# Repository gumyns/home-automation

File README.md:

# Licenses
Code: [Apache 2.0](./LICENSE) ([tl;dr](https://choosealicense.com/licenses/apache-2.0/))

PCB: [CC-BY](./CC-BY.md) ([tl;dr](https://creativecommons.org/licenses/by/4.0/))

# What is it?
STM32 ARM based home automation system. Devices are built with STM32 F0 series microcontrollers (mostly with [STM32F030F4](http://www.st.com/en/microcontrollers/stm32f0x0-value-line.html?querycriteria=productId=LN1826), cheapest one). Project provides also a plugin for [OpenHab2](http://docs.openhab.org/) ([demo](http://demo.openhab.org:8080/start/index)), that allows integration also with other automation systems.

## Architecture
Generally it looks like this:

computer <=> gateway <=> hub <=> device 

On top there's a computer with OpenHab2 running with plugin configured (e.g. PC, RaspberryPi, Odroid, whatever that can run Java8).

Gateway is some cheap ARM based board with Linux, like Rasperry Zero, NanoPi, and communicates with central computer utilizing distributed system built on top of TCP/IP.

Hub is an ARM based board, that can communicate with gateway using any of supported protocols, and can communicate with devices. Amount of ports is configurable.

Device is just a worker (also ARM based board), that communitates with hubs using specific protocol, and provides data to the system.

#### This repository contains following modules
##### - [OpenHab2 plugin](./openhab2)
##### - [C++ server and plugins for gateways](./server)
##### - [PCB layouts and microcontrollers code](./hardware)

# NOTE
This project is in early stage, it's already a working prototype but far from final product.

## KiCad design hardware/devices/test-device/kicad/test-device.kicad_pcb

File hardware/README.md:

## Prerequisites
Download gcc-arm: http://gnuarmeclipse.github.io/toolchain/install/

Generate toolchains and cmake files, call this:
```commandline
python prepare.py
```

Download CubeMX package for STM32F0, or whole STM32CubeMX
```
http://www.st.com/en/embedded-software/stm32cubef0.html
```

## Building
Setup proper toolchain for correct device:
```commandline
mkdir build 
cd build 
cmake .. -DCMAKE_TOOLCHAIN_FILE=../toolchains/STM32F030x6.cmake
```

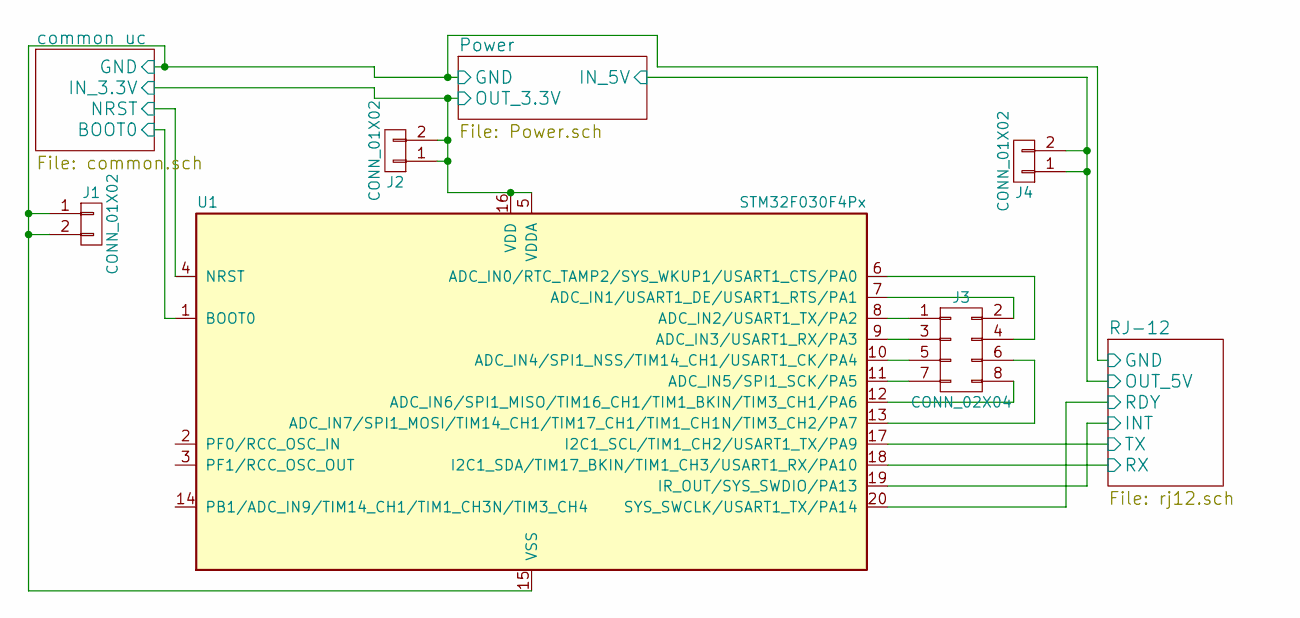
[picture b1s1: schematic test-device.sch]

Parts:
J1, J2, J4: CONN_01X02; Pin_Header_Straight_1x02_Pitch2.54mm
J3: CONN_02X04; Pin_Header_Straight_2x04_Pitch2.54mm
U1: STM32F030F4Px; TSSOP-20_4.4x6.5mm_Pitch0.65mm

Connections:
/Power/GND: J1.1, J1.2, U1.15 (VSS); also elsewhere on the board
/Power/IN_5V: J4.1, J4.2; also elsewhere on the board
/RJ-12/INT: U1.19 (IR_OUT/SYS_SWDIO/PA13); also elsewhere on the board
/RJ-12/RDY: U1.20 (SYS_SWCLK/USART1_TX/PA14); also elsewhere on the board
/RJ-12/RX: U1.18 (I2C1_SDA/TIM17_BKIN/TIM1_CH3/USART1_RX/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); also elsewhere on the board
/RJ-12/TX: U1.17 (I2C1_SCL/TIM1_CH2/USART1_TX/PA9); also elsewhere on the board
/common uc/BOOT0: U1.1 (BOOT0); also elsewhere on the board
/common uc/IN_3.3V: J2.1, J2.2, U1.5 (VDDA), U1.16 (VDD); also elsewhere on the board
/common uc/NRST: U1.4 (NRST); also elsewhere on the board
unnamed: J3.1, U1.8 (ADC_IN2/USART1_TX/PA2)
unnamed: J3.2, U1.7 (ADC_IN1/USART1_DE/USART1_RTS/PA1)
unnamed: J3.3, U1.9 (ADC_IN3/USART1_RX/PA3)
unnamed: J3.4, U1.6 (ADC_IN0/RTC_TAMP2/SYS_WKUP1/USART1_CTS/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)
unnamed: J3.5, U1.10 (ADC_IN4/SPI1_NSS/TIM14_CH1/USART1_CK/PA4)
unnamed: J3.6, U1.13 (ADC_IN7/SPI1_MOSI/TIM14_CH1/TIM17_CH1/T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)
unnamed: J3.7, U1.11 (ADC_IN5/SPI1_SCK/PA5)
unnamed: J3.8, U1.12 (ADC_IN6/SPI1_MISO/TIM16_CH1/TIM1_BKIN/T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)

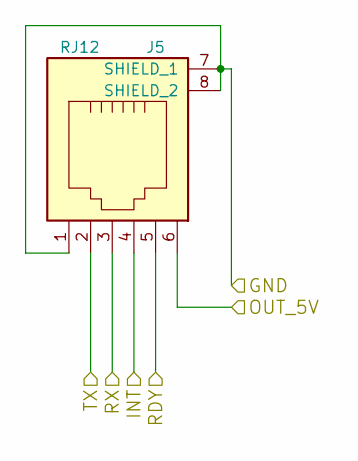
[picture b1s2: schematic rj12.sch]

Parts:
J5: RJ12; molex_95501-2641

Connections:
/Power/GND: J5.1, J5.7 (SHIELD_1), J5.8 (SHIELD_2); also elsewhere on the board
/Power/IN_5V: J5.6; also elsewhere on the board
/RJ-12/INT: J5.4; also elsewhere on the board
/RJ-12/RDY: J5.5; also elsewhere on the board
/RJ-12/RX: J5.3; also elsewhere on the board
/RJ-12/TX: J5.2; also elsewhere on the board

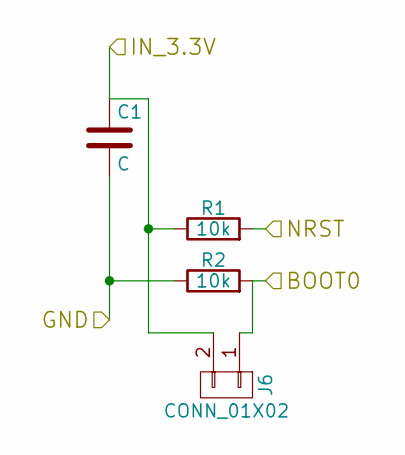
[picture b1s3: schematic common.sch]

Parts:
C1: C; C_1206
J6: CONN_01X02; Pin_Header_Straight_1x02_Pitch2.54mm
R1, R2: 10k; R_0603_HandSoldering

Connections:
/Power/GND: C1.2, R2.1; also elsewhere on the board
/common uc/BOOT0: J6.1, R2.2; also elsewhere on the board
/common uc/IN_3.3V: C1.1, J6.2, R1.1; also elsewhere on the board
/common uc/NRST: R1.2; also elsewhere on the board

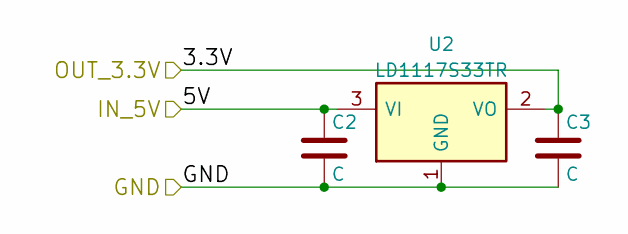
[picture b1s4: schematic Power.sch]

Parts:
C2, C3: C; C_1206
U2: LD1117S33TR; SOT-223-3_TabPin2

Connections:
/Power/GND: C2.2, C3.2, U2.1 (GND); also elsewhere on the board
/Power/IN_5V: C2.1, U2.3 (VI); also elsewhere on the board
/common uc/IN_3.3V: C3.1, U2.2 (VO); also elsewhere on the board

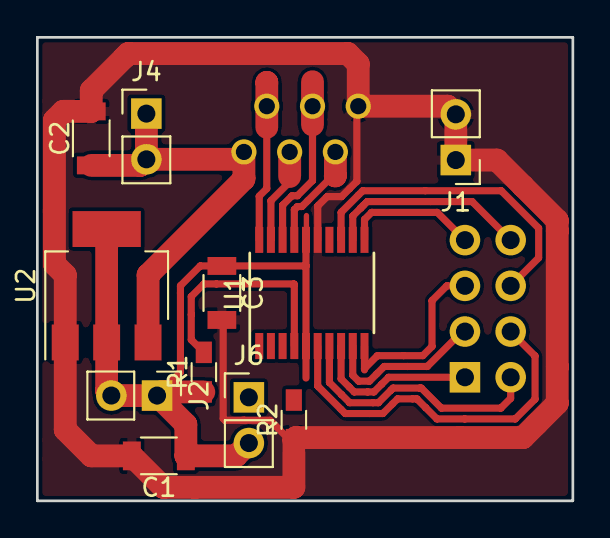
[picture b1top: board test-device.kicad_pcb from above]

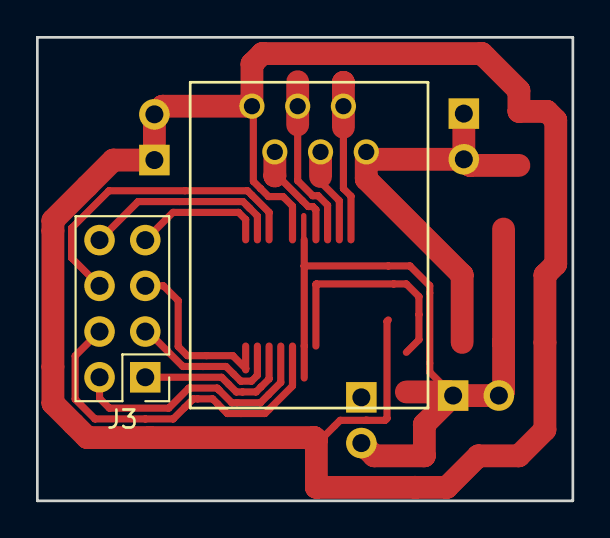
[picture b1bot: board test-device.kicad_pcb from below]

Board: 2 copper layers, 29.8 x 25.8 mm, 13 parts (2 on the bottom side), 17 nets.

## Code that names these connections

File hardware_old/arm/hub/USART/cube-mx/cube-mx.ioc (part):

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Mcu.Name=STM32F042F4Px
Mcu.Package=TSSOP20
Mcu.UserName=STM32F042F4Px
PA0.GPIOParameters=GPIO_Label
PA0.GPIO_Label=ADDR0
PA0.Signal=GPIO_Output
PA1.GPIOParameters=GPIO_Label
PA1.GPIO_Label=ADDR1
PA1.Signal=GPIO_Output
PA10.Mode=Asynchronous
PA10.Signal=USART1_RX
PA14.Signal=GPXTI14
PA2.GPIOParameters=GPIO_Label
PA2.GPIO_Label=ADDR2
PA2.Signal=GPIO_Output
PA3.GPIOParameters=GPIO_Label
PA3.GPIO_Label=ADDR3
PA3.Signal=GPIO_Output
PA4.Mode=NSS_Signal_Hard_Input
PA4.Signal=SPI1_NSS
PA5.Mode=Simplex_Bidirectional_Master
PA5.Signal=SPI1_SCK
PA7.Mode=Simplex_Bidirectional_Master
PA7.Signal=SPI1_MOSI
PA9.Mode=Asynchronous
PA9.Signal=USART1_TX
RCC.SYSCLKFreq_VALUE=8000000
board=cube-mx

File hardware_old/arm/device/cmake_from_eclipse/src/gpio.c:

/**
  ******************************************************************************
  * File Name          : gpio.c
  * Description        : This file provides code for the configuration
  *                      of all used GPIO pins.
  ******************************************************************************
  *
  * COPYRIGHT(c) 2017 STMicroelectronics
  *
  * Redistribution and use in source and binary forms, with or without modification,
  * are permitted provided that the following conditions are met:
  *   1. Redistributions of source code must retain the above copyright notice,
  *      this list of conditions and the following disclaimer.
  *   2. Redistributions in binary form must reproduce the above copyright notice,
  *      this list of conditions and the following disclaimer in the documentation
  *      and/or other materials provided with the distribution.
  *   3. Neither the name of STMicroelectronics nor the names of its contributors
  *      may be used to endorse or promote products derived from this software
  *      without specific prior written permission.
  *
  * THIS SOFTWARE IS PROVIDED BY THE COPYRIGHT HOLDERS AND CONTRIBUTORS "AS IS"
  * AND ANY EXPRESS OR IMPLIED WARRANTIES, INCLUDING, BUT NOT LIMITED TO, THE
  * IMPLIED WARRANTIES OF MERCHANTABILITY AND FITNESS FOR A PARTICULAR PURPOSE ARE
  * DISCLAIMED. IN NO EVENT SHALL THE COPYRIGHT HOLDER OR CONTRIBUTORS BE LIABLE
  * FOR ANY DIRECT, INDIRECT, INCIDENTAL, SPECIAL, EXEMPLARY, OR CONSEQUENTIAL
  * DAMAGES (INCLUDING, BUT NOT LIMITED TO, PROCUREMENT OF SUBSTITUTE GOODS OR
  * SERVICES; LOSS OF USE, DATA, OR PROFITS; OR BUSINESS INTERRUPTION) HOWEVER
  * CAUSED AND ON ANY THEORY OF LIABILITY, WHETHER IN CONTRACT, STRICT LIABILITY,
  * OR TORT (INCLUDING NEGLIGENCE OR OTHERWISE) ARISING IN ANY WAY OUT OF THE USE
  * OF THIS SOFTWARE, EVEN IF ADVISED OF THE POSSIBILITY OF SUCH DAMAGE.
  *
  ******************************************************************************
  */

/* Includes ------------------------------------------------------------------*/
#include "gpio.h"
/* USER CODE BEGIN 0 */

/* USER CODE END 0 */

/*----------------------------------------------------------------------------*/
/* Configure GPIO                                                             */
/*----------------------------------------------------------------------------*/
/* USER CODE BEGIN 1 */

/* USER CODE END 1 */

/** Configure pins as 
        * Analog 
        * Input 
        * Output
        * EVENT_OUT
        * EXTI
        * Free pins are configured automatically as Analog (this feature is enabled through 
        * the Code Generation settings)
*/
void MX_GPIO_Init(void)
{

  GPIO_InitTypeDef GPIO_InitStruct;

  /* GPIO Ports Clock Enable */
  __HAL_RCC_GPIOF_CLK_ENABLE();
  __HAL_RCC_GPIOA_CLK_ENABLE();
  __HAL_RCC_GPIOB_CLK_ENABLE();

  /*Configure GPIO pins : PF0 PF1 */
  GPIO_InitStruct.Pin = GPIO_PIN_0|GPIO_PIN_1;
  GPIO_InitStruct.Mode = GPIO_MODE_ANALOG;
  GPIO_InitStruct.Pull = GPIO_NOPULL;
  HAL_GPIO_Init(GPIOF, &GPIO_InitStruct);

  /*Configure GPIO pins : PA2 PA3 PA4 PA5 
                           PA6 PA7 PA9 PA10 
                           PA13 PA14 */
  GPIO_InitStruct.Pin = GPIO_PIN_2|GPIO_PIN_3|GPIO_PIN_4|GPIO_PIN_5 
                          |GPIO_PIN_6|GPIO_PIN_7|GPIO_PIN_9|GPIO_PIN_10 
                          |GPIO_PIN_13|GPIO_PIN_14;
  GPIO_InitStruct.Mode = GPIO_MODE_ANALOG;
  GPIO_InitStruct.Pull = GPIO_NOPULL;
  HAL_GPIO_Init(GPIOA, &GPIO_InitStruct);

  /*Configure GPIO pin : PB1 */
  GPIO_InitStruct.Pin = GPIO_PIN_1;
  GPIO_InitStruct.Mode = GPIO_MODE_ANALOG;
  GPIO_InitStruct.Pull = GPIO_NOPULL;
  HAL_GPIO_Init(GPIOB, &GPIO_InitStruct);

}

/* USER CODE BEGIN 2 */

/* USER CODE END 2 */

/**
  * @}
  */

/**
  * @}
  */

/************************ (C) COPYRIGHT STMicroelectronics *****END OF FILE****/

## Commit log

2017-04-01 Update LICENSE
2017-04-01 init
2017-04-01 License
2017-04-01 Create CC-BY
2017-04-01 Rename CC-BY to CC-BY.md
2017-04-01 some info about project
2017-04-02 4 port shield pcb
2017-04-02 updated uart hub pcb
2017-04-04 fixed port address in hub
2017-04-16 some build scripts
2017-04-16 some build scripts
    new file: .gitignore
    new file: 00_boost.py
    new file: 01_json.py
    new file: 02_zeromq.py
    new file: dep_lib.py
    modified: ../resolveDependencies.py
2017-04-16 cleanups, more build scripts
2017-04-16 complete build script for server
2017-04-16 docs
2017-04-16 cleanup
2017-04-17 cmake changes for bigger project support
2017-04-17 same convention used for all factories
2017-04-17 script fix
2017-04-17 make fix
2017-04-17 simplified cmake scrips
2017-04-17 proper config
2017-04-17 build all script + 'tests'
2017-04-17 simplify tests
2017-04-17 preparations for CMake support for embedded code
2017-04-19 arm toolchain generator
2017-04-20 added some working cmake embedded project as reference
2017-04-20 make one common standard library for all embedded projects
2017-04-20 linker scripts
2017-06-13 deprecated old hardware stuff, there will be new soon
2017-06-13 'readme'
2017-06-14 hardware deps
2017-06-23 cmake fix
2017-06-25 toolchain fix
2017-06-25 toolchain generator
2017-06-26 download flashing tool
2017-06-26 arm cmake init
2017-06-27 arm cmake
2017-06-27 toolchain changes
2017-06-27 generate libs directories
2017-06-27 find cmsis and hal added
2017-06-27 gitignore
2017-06-27 window sensor project
2017-06-28 change window sensor to cpp
2017-06-28 added i2c to window sensor
2017-06-28 added scriptable i2c address
2017-06-28 naming change, cleanup
2017-06-28 int pullup
2017-06-28 interrupts
2017-06-29 generate startup files
2017-06-29 add startup files to project
2017-06-29 some cleanups
2017-06-29 build all possible addresses script
2017-06-29 added interrupt
2017-06-29 some improvements to build script
2017-06-30 hub project
2017-08-01 test of usart as main protocol
2017-12-03 kicad templates
2017-12-03 test device board
2017-12-12 board fixes
